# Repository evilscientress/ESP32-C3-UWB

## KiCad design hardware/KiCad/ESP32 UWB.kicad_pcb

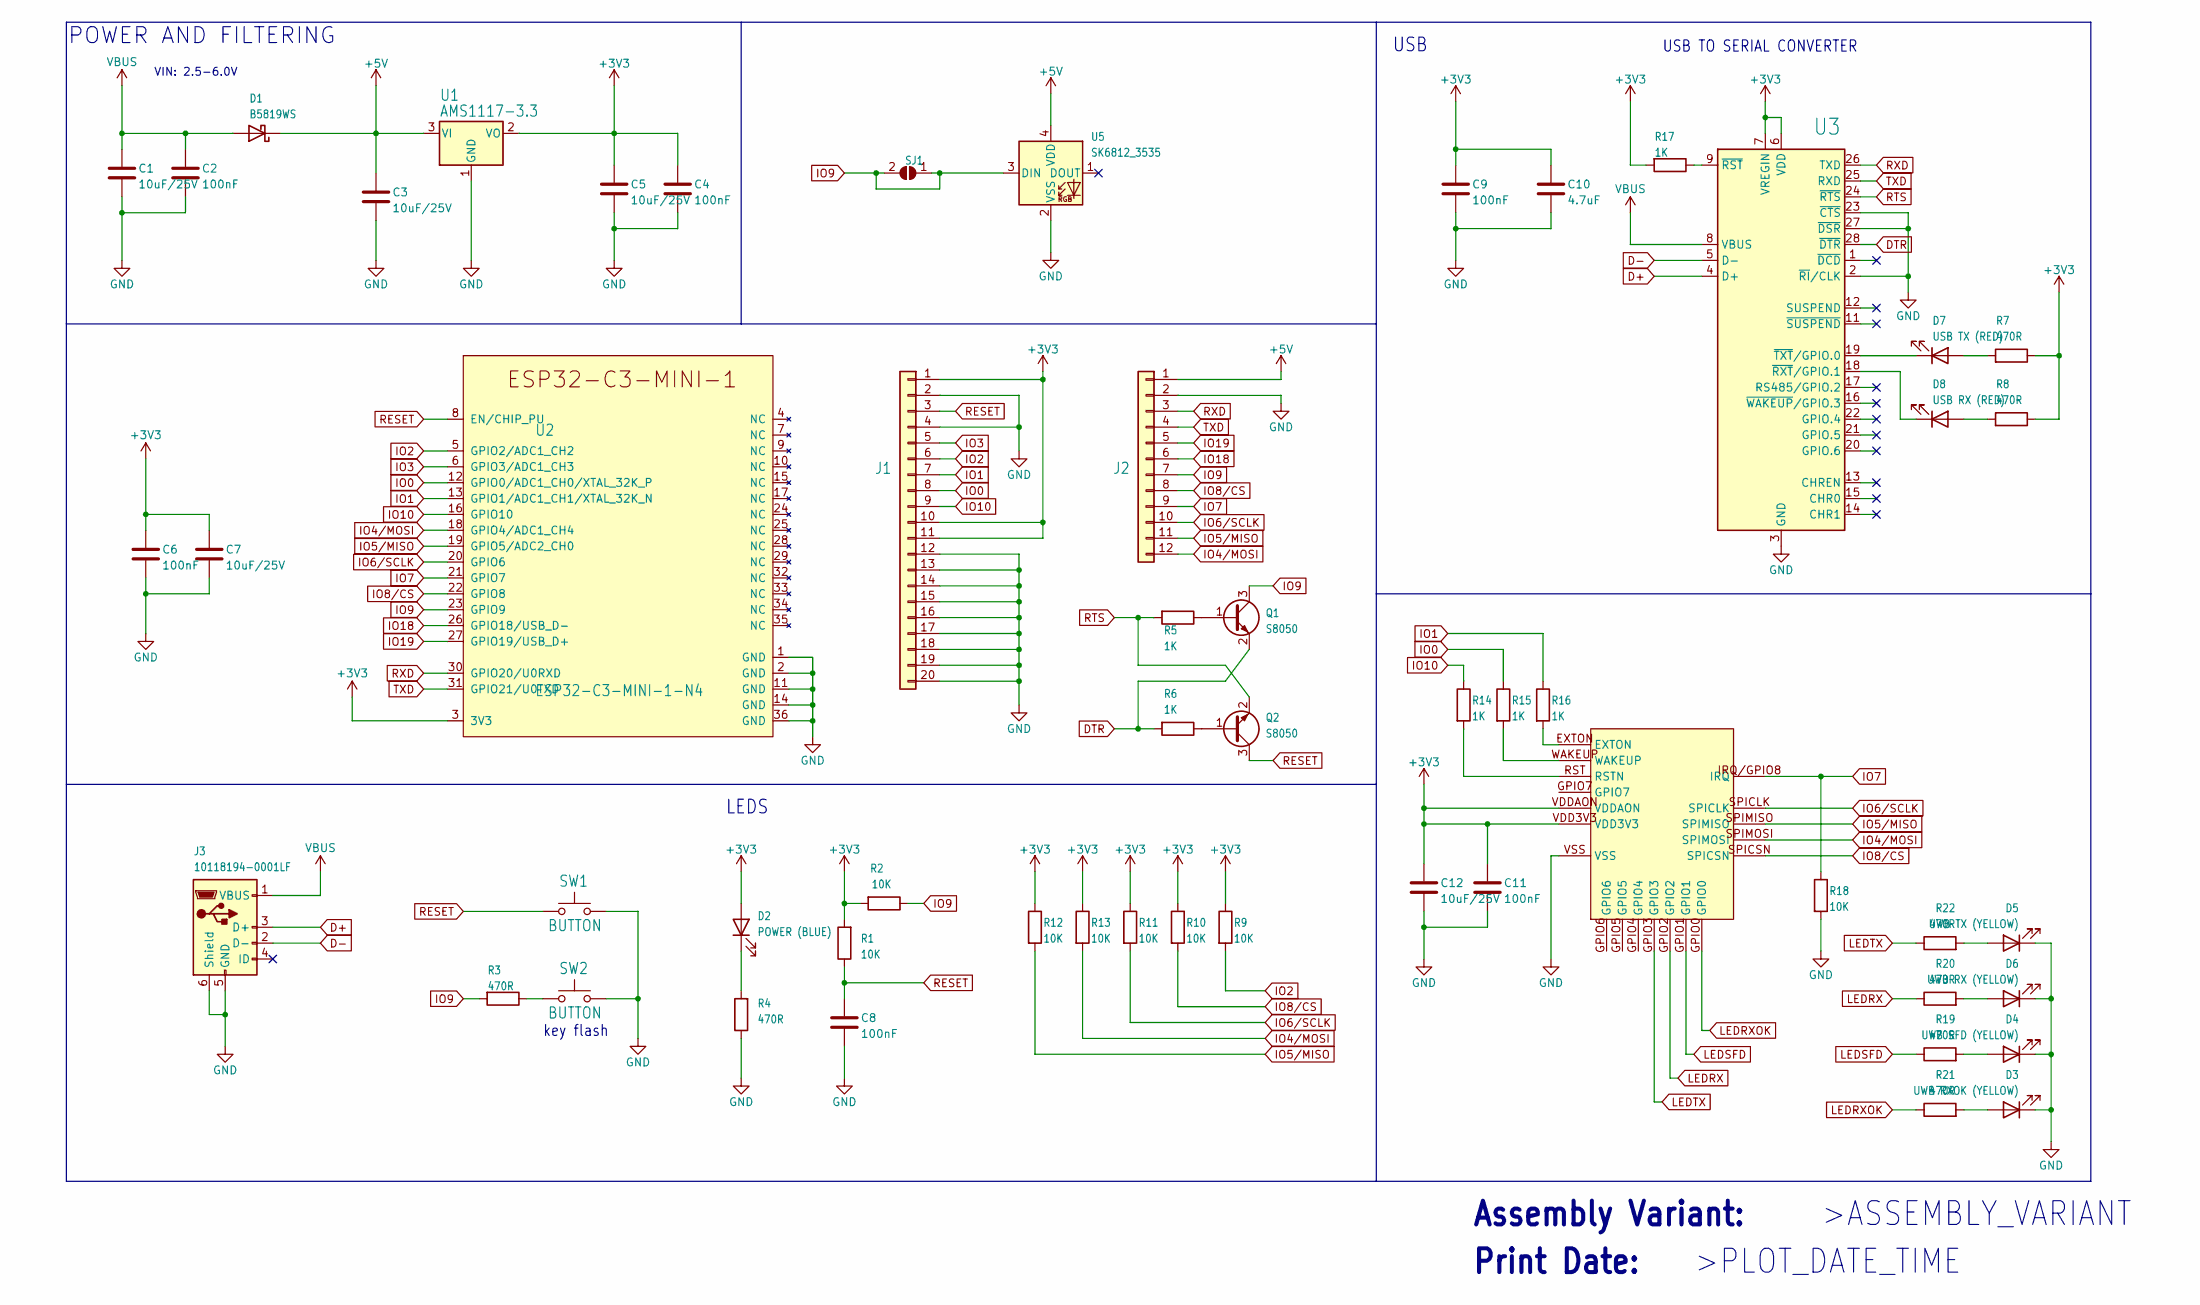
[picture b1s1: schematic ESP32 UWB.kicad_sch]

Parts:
C1, C3, C5, C7, C12: 10uF/25V; C_0603_1608Metric_Pad1.08x0.95mm_HandSolder; Part CL10X106MO8NRNC; LCSC C96446
C2, C4, C6, C8, C9, C11: 100nF; C_0603_1608Metric_Pad1.08x0.95mm_HandSolder; Part CL10B104KB8NNWC; LCSC C14663
C10: 4.7uF; C_0603_1608Metric_Pad1.08x0.95mm_HandSolder; Part CL10A475KO8NNNC; LCSC C19666
D1: B5819WS; D_SOD-323_HandSoldering; Part NSVR1020MW2T1G; LCSC C191023
D2: POWER (BLUE); LED_0805_2012Metric_Pad1.15x1.40mm_HandSolder; Part 150080BS75000; LCSC C2293
D3: UWB RXOK (YELLOW); LED_0805_2012Metric_Pad1.15x1.40mm_HandSolder; Part LY R976-PS-36; LCSC C2296
D4: UWB SFD (YELLOW); LED_0805_2012Metric_Pad1.15x1.40mm_HandSolder; Part LY R976-PS-36; LCSC C2296
D5: UWB TX (YELLOW); LED_0805_2012Metric_Pad1.15x1.40mm_HandSolder; Part LY R976-PS-36; LCSC C2296
D6: UWB RX (YELLOW); LED_0805_2012Metric_Pad1.15x1.40mm_HandSolder; Part LY R976-PS-36; LCSC C2296
D7: USB TX (RED); LED_0603_1608Metric_Pad1.05x0.95mm_HandSolder; Part SML-D12U1WT86; LCSC C2286
D8: USB RX (RED); LED_0603_1608Metric_Pad1.05x0.95mm_HandSolder; Part SML-D12U1WT86; LCSC C2286
J1: HEADER-20P-2.54; PinHeader_1x20_P2.54mm_Vertical; Part PH1-20-UA; LCSC C50981
J2: HEADER-12P-2.54; PinHeader_1x12_P2.54mm_Vertical; Part PH1-12-UA; LCSC C225487
J3: 10118194-0001LF; USB_Micro-B_Amphenol_10118194_Horizontal; Part 10118194-0001LF; LCSC C132563
Q1, Q2: S8050; SOT-23; Part SS8050-G; LCSC C2146
R1, R2, R9, R10, R11, R12, R13, R18: 10K; R_0603_1608Metric_Pad0.98x0.95mm_HandSolder; Part RMCF0603JT10K0; LCSC C25804
R3, R4, R7, R8, R19, R20, R21, R22: 470R; R_0603_1608Metric_Pad0.98x0.95mm_HandSolder; Part RMCF0603JT470R; LCSC C23179
R5, R6, R14, R15, R16, R17: 1K; R_0603_1608Metric_Pad0.98x0.95mm_HandSolder; Part RMCF0603JJ1K00; LCSC C21190
SJ1: SJS; SolderJumper-2_P1.3mm_Open_TrianglePad1.0x1.5mm
SW1, SW2: BUTTON; SW_Push_3x4mm; Part PTS820J15MSMTRLFS; LCSC C720477
U1: AMS1117-3.3; SOT-223-3_TabPin2; Part NCP1117LPST33T3G; LCSC C6186
U2: ESP32-C3-MINI-1-N4; ESP32-C3-MINI-1_Hand-Soldering; Part ESP32-C3-MINI-1-N4; LCSC C2838502
U3: SILICON_LABS_CP2102N-A01-GQFN28SILICON_LABS_CP210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; QFN-28-1EP_5x5mm_P0.5mm_EP3.35x3.35mm; Part CP2102N-A02-GQFN28; LCSC C6568
U4: BU01; Part BU01; LCSC C503604
U5: SK6812_3535; LED_SK6812MINI_PLCC4_3.5x3.5mm_P1.75mm; Part 2659

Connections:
+3V3: C4.1, C5.1, C6.1, C7.1, C9.1, C10.1, C11.1, C12.1, D2.2 (A), J1.1, J1.10, J1.11, R1.2, R2.2, R7.1, R8.1, R9.1, R10.1, R11.1, R12.1, R13.1, R17.2, U1.2 (VO), U2.3 (3V3), U3.6 (VDD), U3.7 (VREGIN), U4.VDD3V3, U4.VDDAON
+5V: C3.1, D1.1 (K), J2.1, U1.3 (VI), U5.4 (VDD)
D+: J3.3 (D+), U3.4 (D+)
D-: J3.2 (D-), U3.5 (D-)
DTR: Q1.2 (E), R6.2, U3.28 (~DTR)
GND: C1.2, C2.2, C3.2, C4.2, C5.2, C6.2, C7.2, C8.2, C9.2, C10.2, C11.2, C12.2, D3.1 (K), D4.1 (K), D5.1 (K), D6.1 (K), J1.2, J1.4, J1.12, J1.13, J1.14, J1.15, J1.16, J1.17, J1.18, J1.19, J1.20, J2.2, J3.5 (GND), J3.6 (Shield), R4.1, R18.2, SW1.2, SW2.2, U1.1 (GND), U2.1 (GND), U2.2 (GND), U2.11 (GND), U2.14 (GND), U2.36 (GND), U3.2 (~RI/CLK), U3.3 (GND), U3.23 (~CTS), U3.27 (~DSR), U3.29 (GND), U4.VSS, U5.2 (VSS)
IO0: J1.8, R15.1, U2.12 (GPIO0/ADC1_CH0/XTAL_32K_P)
IO1: J1.7, R16.1, U2.13 (GPIO1/ADC1_CH1/XTAL_32K_N)
IO2: J1.6, R9.2, U2.5 (GPIO2/ADC1_CH2)
IO3: J1.5, U2.6 (GPIO3/ADC1_CH3)
IO4/MOSI: J2.12, R13.2, U2.18 (GPIO4/ADC1_CH4), U4.SPIMOSI
IO5/MISO: J2.11, R12.2, U2.19 (GPIO5/ADC2_CH0), U4.SPIMISO
IO6/SCLK: J2.10, R11.2, U2.20 (GPIO6), U4.SPICLK
IO7: J2.9, R18.1, U2.21 (GPIO7), U4.IRQ/GPIO8 (IRQ)
IO8/CS: J2.8, R10.2, U2.22 (GPIO8), U4.SPICSN
IO9: J2.7, Q1.3 (C), R2.1, R3.2, SJ1.1 (A), SJ1.2 (B), U2.23 (GPIO9), U5.3 (DIN)
IO10: J1.9, R14.1, U2.16 (GPIO10)
IO18: J2.6, U2.26 (GPIO18/USB_D-)
IO19: J2.5, U2.27 (GPIO19/USB_D+)
LEDRX: R20.1, U4.GPIO2
LEDRXOK: R21.1, U4.GPIO0
LEDSFD: R19.1, U4.GPIO1
LEDTX: R22.1, U4.GPIO3
unnamed: D2.1 (K), R4.2
unnamed: D3.2 (A), R21.2
unnamed: D4.2 (A), R19.2
unnamed: D5.2 (A), R22.2
unnamed: D6.2 (A), R20.2
unnamed: D7.1 (K), U3.19 (~TXT/GPIO.0)
unnamed: D7.2 (A), R7.2
unnamed: D8.1 (K), U3.18 (~RXT/GPIO.1)
unnamed: D8.2 (A), R8.2
unnamed: Q1.1 (B), R5.1
unnamed: Q2.1 (B), R6.1
unnamed: R3.1, SW2.1
unnamed: R14.2, U4.RST (RSTN)
unnamed: R15.2, U4.WAKEUP
unnamed: R16.2, U4.EXTON
unnamed: R17.1, U3.9 (~RST)
RESET: C8.1, J1.3, Q2.3 (C), R1.1, SW1.1, U2.8 (EN/CHIP_PU)
RTS: Q2.2 (E), R5.2, U3.24 (~RTS)
RXD: J2.3, U2.30 (GPIO20/U0RXD), U3.26 (TXD)
TXD: J2.4, U2.31 (GPIO21/U0TXD), U3.25 (RXD)
VBUS: C1.1, C2.1, D1.2 (A), J3.1 (VBUS), U3.8 (VBUS)

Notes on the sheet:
VIN: 2.5-6.0V
>PLOT_DATE_TIME
LEDS
USB TO SERIAL CONVERTER
Assembly Variant:
Print Date:
>ASSEMBLY_VARIANT
USB
key flash
POWER AND FILTERING

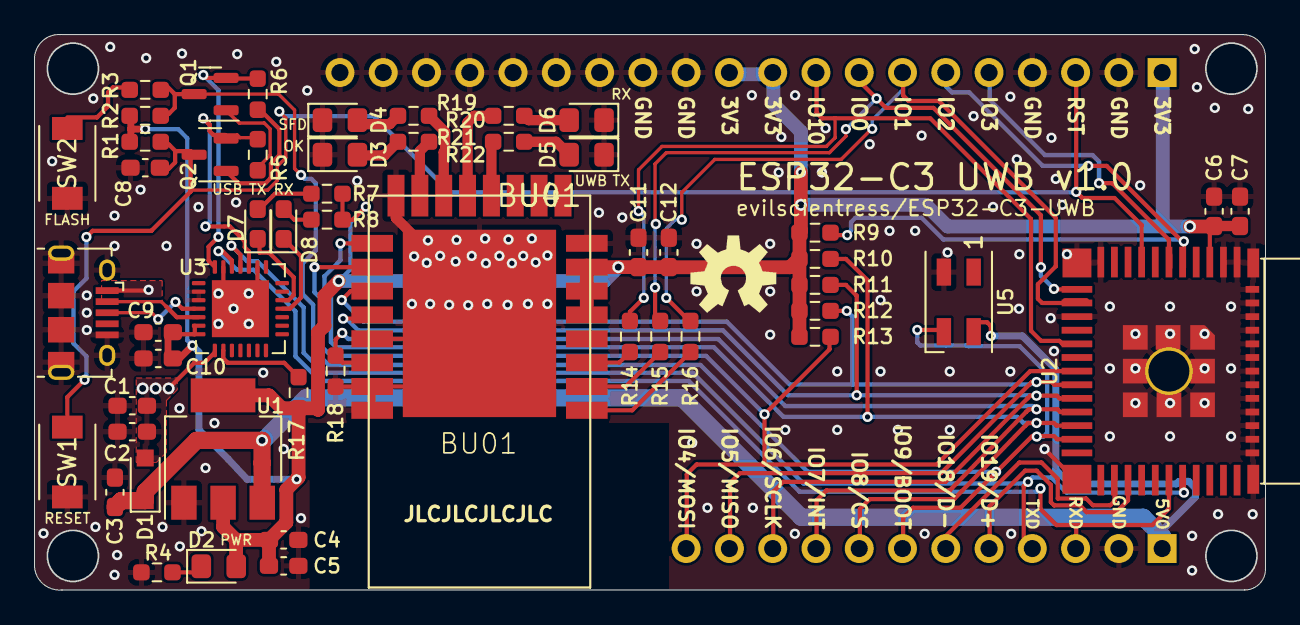
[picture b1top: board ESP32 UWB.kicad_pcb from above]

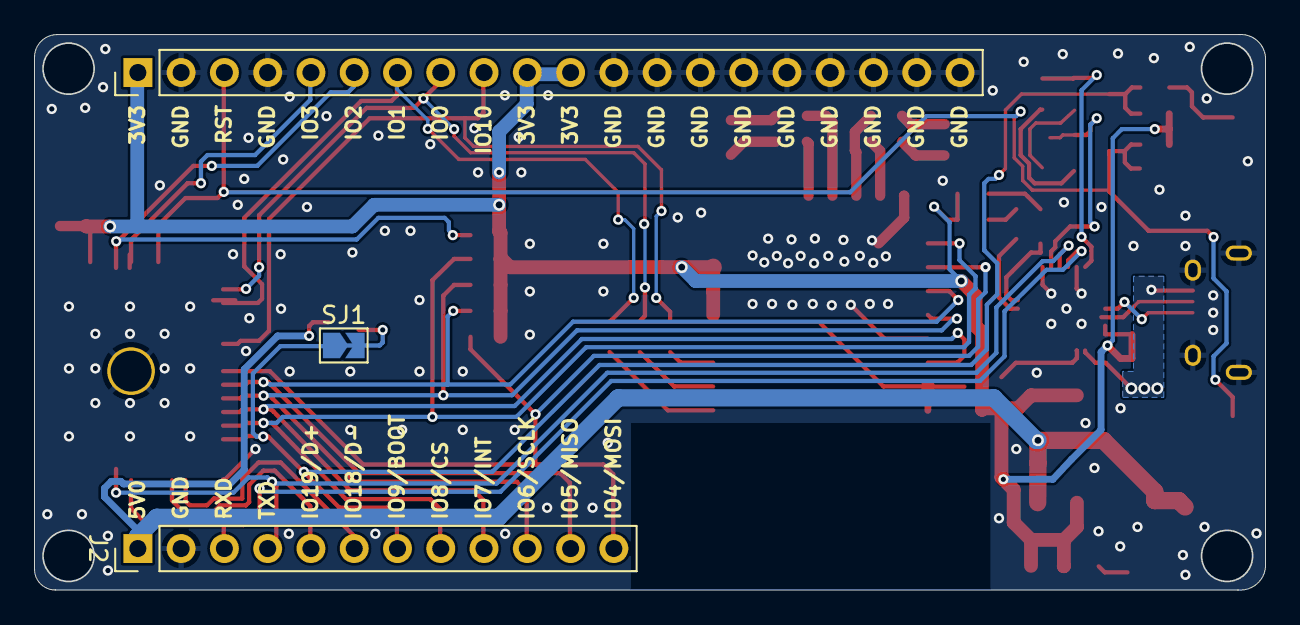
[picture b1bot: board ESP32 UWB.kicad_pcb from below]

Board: 2 copper layers, 72.2 x 32.6 mm, 56 parts (3 on the bottom side), 44 nets.

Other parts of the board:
U$1: OSHW-LOGO-M

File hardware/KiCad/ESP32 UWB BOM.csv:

Qty,Reference(s),Value,Footprint,Comment,LCSC,Meaning,Part
5,"C1, C3, C5, C7, C12",10uF/25V,Capacitor_SMD:C_0603_1608Metric_Pad1.08x0.95mm_HandSolder,,C96446,,CL10X106MO8NRNC
6,"C2, C4, C6, C8, C9, C11",100nF,Capacitor_SMD:C_0603_1608Metric_Pad1.08x0.95mm_HandSolder,,C14663,,CL10B104KB8NNWC
1,C10,4.7uF,Capacitor_SMD:C_0603_1608Metric_Pad1.08x0.95mm_HandSolder,,C19666,,CL10A475KO8NNNC
1,D1,B5819WS,Diode_SMD:D_SOD-323_HandSoldering,,C191023,,NSVR1020MW2T1G
1,D2,POWER (BLUE),LED_SMD:LED_0805_2012Metric_Pad1.15x1.40mm_HandSolder,,C2293,PWR,150080BS75000
1,D3,UWB RXOK (YELLOW),LED_SMD:LED_0805_2012Metric_Pad1.15x1.40mm_HandSolder,,C2296,RXOK,LY R976-PS-36
1,D4,UWB SFD (YELLOW),LED_SMD:LED_0805_2012Metric_Pad1.15x1.40mm_HandSolder,,C2296,SFD,LY R976-PS-36
1,D5,UWB TX (YELLOW),LED_SMD:LED_0805_2012Metric_Pad1.15x1.40mm_HandSolder,,C2296,TX,LY R976-PS-36
1,D6,UWB RX (YELLOW),LED_SMD:LED_0805_2012Metric_Pad1.15x1.40mm_HandSolder,,C2296,RX,LY R976-PS-36
1,D7,USB TX (RED),LED_SMD:LED_0603_1608Metric_Pad1.05x0.95mm_HandSolder,,C2286,TX,SML-D12U1WT86
1,D8,USB RX (RED),LED_SMD:LED_0603_1608Metric_Pad1.05x0.95mm_HandSolder,,C2286,RX,SML-D12U1WT86
1,J1,HEADER-20P-2.54,Connector_PinHeader_2.54mm:PinHeader_1x20_P2.54mm_Vertical,,C50981,,PH1-20-UA
1,J2,HEADER-12P-2.54,Connector_PinHeader_2.54mm:PinHeader_1x12_P2.54mm_Vertical,,C225487,,PH1-12-UA
1,J3,10118194-0001LF,Connector_USB:USB_Micro-B_Amphenol_10118194_Horizontal,,C132563,,10118194-0001LF
2,"Q1, Q2",S8050,Package_TO_SOT_SMD:SOT-23,,C2146,,SS8050-G
8,"R1, R2, R9, R10, R11, R12, R13, R18",10K,Resistor_SMD:R_0603_1608Metric_Pad0.98x0.95mm_HandSolder,,C25804,,RMCF0603JT10K0
8,"R3, R4, R7, R8, R19, R20, R21, R22",470R,Resistor_SMD:R_0603_1608Metric_Pad0.98x0.95mm_HandSolder,,C23179,,RMCF0603JT470R
6,"R5, R6, R14, R15, R16, R17",1K,Resistor_SMD:R_0603_1608Metric_Pad0.98x0.95mm_HandSolder,,C21190,,RMCF0603JJ1K00
2,"SW1, SW2",BUTTON,ESP32 UWB:SW_Push_3x4mm,,C720477,,PTS820J15MSMTRLFS
1,U1,AMS1117-3.3,Package_TO_SOT_SMD:SOT-223-3_TabPin2,Uncommon Pinout for SOT-223 LDOs!,C6186,,NCP1117LPST33T3G
1,U2,ESP32-C3-MINI-1-N4,Espressif:ESP32-C3-MINI-1_Hand-Soldering,,C2838502,,ESP32-C3-MINI-1-N4
1,U3,SILICON_LABS_CP2102N-A01-GQFN28SILICON_LABS_CP2102N-A01-GQFN28_0_3,Package_DFN_QFN:QFN-28-1EP_5x5mm_P0.5mm_EP3.35x3.35mm,,C6568,,CP2102N-A02-GQFN28
1,U4,BU01,ESP32 UWB:BU01,AliExpress,C503604,,BU01
1,U5,SK6812_3535,LED_SMD:LED_SK6812MINI_PLCC4_3.5x3.5mm_P1.75mm,"optional, search ""SK6812 3535"" on Aliexpress, also Adafruit #2686",,,2659

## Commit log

2022-01-05 swaped ESP module to ESP32-C3-MINI
2022-01-05 schematic cleanup and pdf export
2022-01-05 added gitignore file
2022-01-05 renamed pcb files, updated gerber package
2022-01-06 switched various parts to more newer or more available part, moved all to the front
    Switched Parts:
    * USB-Serial Converter CP2104 -> CP2102N
    * 3.3V LDO
    * Micro USB Connector
    All parts are now on the front side which means expensive double sided assembly is no longer needed.
2022-01-06 switched resistor and capacitor footprints, placed labels
2022-01-06 Added WS2812b led for status display
2022-01-06 fixed floating input pins
2022-01-06 added solder jumper for optionally disabling the ws2812 led
2022-01-06 updated gerber files and schematic pdf
2022-01-06 added images of top and bottom of the pcb
2022-01-07 Updated SJ Package to my own (smaller) version
2022-01-07 fixed device prefixes, removed duplicate supply symbols
2022-01-07 renumbered parts
2022-01-07 replaced footprint of C7
2022-01-07 updated library
2022-01-07 replaced WS2812 with SK6812-mini-e
2022-01-07 added production files (gerber, bom, cpl) for latest version
2022-01-09 fixed schematic pdf
2022-01-09 added assembly variant without USB serial converter
2022-01-09 add version converted to KiCad
2022-01-15 update schematic to use built-in kicad symbols
2022-01-15 change all footprints in schematic
2022-01-15 fox pcb
2022-01-15 tweak pcb and fix all DRC errors
2022-01-15 first silkscreen tweaks
2022-01-15 more tweaks
2022-01-15 tweak silkscreen and 3d model
2022-01-15 tweak silkscreen orientation and more
2022-01-15 swap pushbuttons
2022-01-15 clean up schematic
2022-01-15 add keepout zone and labels for LEDs
2022-01-15 make DRC happy
2022-01-15 remove cache
2022-01-15 add kicad gitignore
2022-01-15 remove unused symbols and footprints
2022-01-16 further cleanup and improvment of the KiCad version of the PCB
2022-01-16 label buttons
2022-01-16 add JLCJLCJLCJLC
2022-01-16 adjust silkscreen
2022-01-16 add BOM fields and tweak symbols and parts
2022-01-16 tweak bom some more
2022-01-16 add files for JLCPCB
2022-01-16 more fabrication files
